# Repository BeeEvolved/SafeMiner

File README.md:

# SafeMiner
SafeMiner is a hardware design aimed at creating a safety system for Bitcoin mining hardware. The Design incorporates fire detection and automatic shutdown to ensure the safety of miners and mining operations.  Including home miners that often mine from home or a garage. Protecting personal property, yourself, and your family.

### Early detection and prevention
The primary goal is to detect an event at the spark, arc, thermal spike or smoke phase before it can become true blazing fire. It’s obviously going to be a case-by-case scenario, but cutting the power certainly could prevent unpleasant outcomes. The wording of “fire detection” of the SafeMiner might be a little confusing for some, but the overall mission is to detect the earliest catalyst of a fire, sudden thermal spike, sparks, or arcs on a hashboard or Bitcoin miner to mitigate losses or damage.

### SafeMiner hardware  Design

SafeMiner is a hardware design project aims at creating a safety system for Bitcoin mining hardware. The design incorporates fire detection and an automatic shutdown mechanism to ensure the safety of miners and mining operations.

## Future SafeMiner designs 
Currently, the flagship design is tailored for the QuadAxe configuration, housing four Bitaxes within an S9 chassis. Following extensive testing, future designs will be adapted to popular Bitcoin miners such as the Antminer S19, S21 and T21.

## Overview

This repository contains the hardware designs of the SafeMiner project. The design implements various safety features, including automatic shutdown, to protect Bitcoin mining operations from fire.

## Fire Sensor and Automatic shutdown Operation Explanation
### Fire Detection and Safety Mechanism

- **Q1 (Flame Sensor):** This component detects fires near the mining hardware, hashboard or inside chassis. When activated, its signal pin connects to the gate pin of the MOSFET.
- **Gate (MOSFET - IRLZ44NPBF):** The MOSFET controls power distribution to the mining hardware. Its gate pin receives the signal from the flame sensor. When a fire is detected, the MOSFET shuts off power to the connected hardware, preventing potential hazards.

## BOM Component Part Numbers

The following components are used in the SafeMiner PCB design:

- **C1:** 10uF capacitor (Digi-Key: 1189-2294-ND)
- **R1:** 5K resistor (Digi-Key: MFP25SBBE52-5K-ND)
- **R2:** 33K resistor (Digi-Key: 13-CFR-25JR-52-33KCT-ND)
- **D1:** 1N4007 diode (Digi-Key: 1N4007GDICT-ND)
- **Gate (MOSFET):** IRLZ44NPBF (Digi-Key: IRLZ44NPBF-ND)
- **Q1:** Flame sensor (Digi-Key: 399-USEQFCSA455100-ND)
- **RV1:** 5K trimmer potentiometer (Digi-Key: 3362P-502LF-ND)
- **J1:** Terminal blocks (Digi-Key: A113320-ND)

## Disclaimer

**Important Note:** This PCB design is currently untested and NOT ready for usage without proper testing. We strongly advise against attempting to use or manufacture the design until it has been thoroughly tested and validated for reliability and safety.

We are currently in the process of ordering PCBs/parts and will conduct extensive testing upon their arrival. The results of our testing will be published to this repository, providing transparency and ensuring the design's suitability for production use.

Thank you for your understanding and patience as we work to ensure the safety and reliability of these designs.

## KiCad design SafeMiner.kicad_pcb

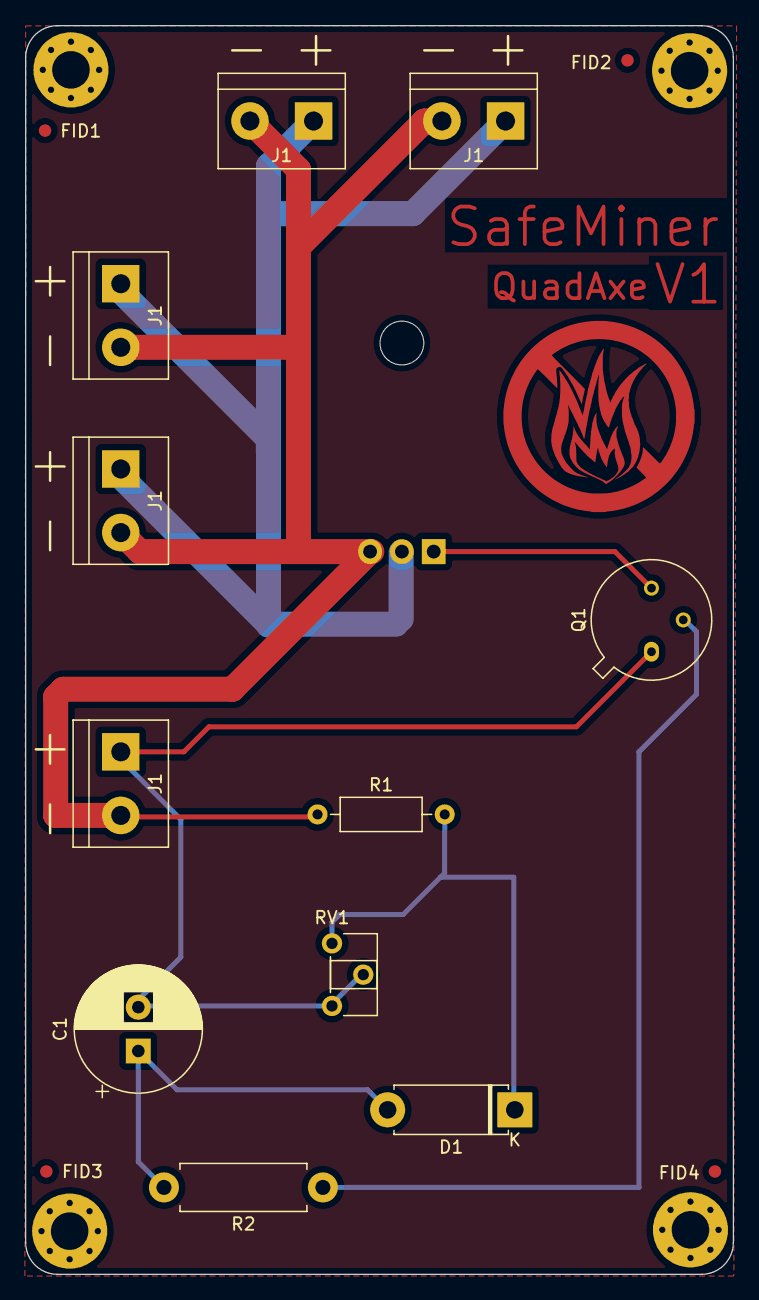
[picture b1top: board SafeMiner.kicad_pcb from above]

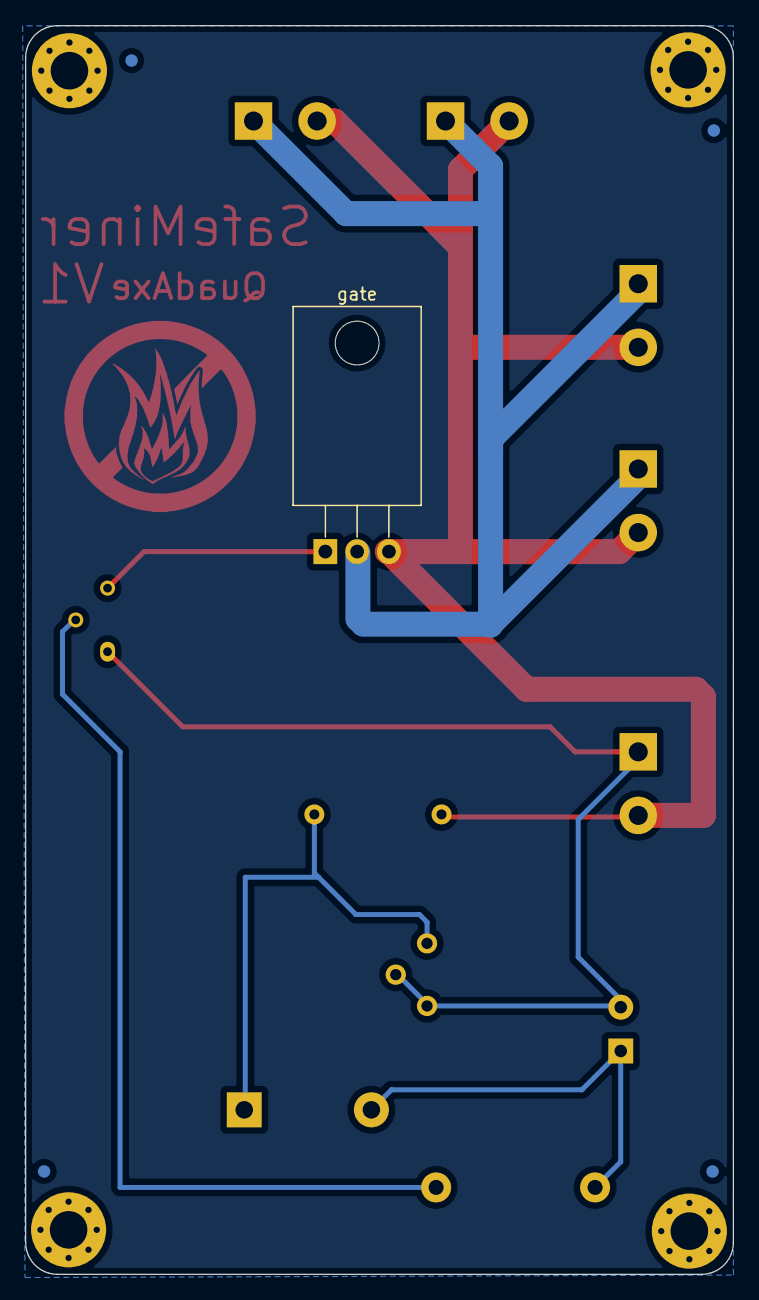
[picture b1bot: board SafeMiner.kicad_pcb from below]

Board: 2 copper layers, 56.5 x 99.8 mm, 24 parts (5 on the bottom side), 6 nets.

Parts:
C1: 10uF; CP_Radial_D10.0mm_P3.50mm
D1: 1N4007; D_5W_P10.16mm_Horizontal
FID1, FID2, FID3, FID4, FID5, FID6, FID7, FID8: Fiducial; Fiducial_1mm_Mask2mm
H7, H8, H9, H10: MountingHole_Pad; MountingHole_3mm_Pad_Via
J1, J1#2, J1#3, J1#4, J1#5: 282837-2; TerminalBlock_bornier-2_P5.08mm
Q1: FLAME SENSOR; TO-39-3
R1: RES 5K; R_Axial_DIN0207_L6.3mm_D2.5mm_P10.16mm_Horizontal
R2: 33K; R_Axial_DIN0411_L9.9mm_D3.6mm_P12.70mm_Horizontal
RV1: TRIMMER; Potentiometer_ACP_CA6-H2,5_Horizontal
gate: MOSFET; TO-220-3_Horizontal_TabDown

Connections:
Fire-Sensor-GND: Q1.2 (B), R2.1
GND: C1.2, J1.1, J1#2.1, J1#3.1, J1#4.1, J1#5.1, Q1.1 (E), RV1.2, RV1.3, gate.Pin 2 power
Net-C1: C1.1, D1.2 (A), R2.2
Net-D1: D1.1 (K), R1.2, RV1.1
Net-Fire-Signal-Shutoff: Q1.3 (C), gate.Pin 1 Gate
VCC: J1.2, J1#2.2, J1#3.2, J1#4.2, J1#5.2, R1.1, gate.3

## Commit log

2024-04-14 SafeMiner Kicad "QuadAxe" design
2024-04-14 SafeMiner QuadAxe images
2024-04-14 SafeMinerLogo
2024-04-14 Create Antminer_S19_S21_T21
2024-04-14 added ibom html
2024-04-14 bom csv
